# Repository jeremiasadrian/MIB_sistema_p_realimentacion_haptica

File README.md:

# MIB_sistema_p_realimentacion_haptica
**DESCRIPCION DEL REPOSITORIO.**
<p align="justify">
El presente respositorio corresponde al Proyecto asociado a la Tesis de la Maestría en Ingeniería Biomédica de la FI-UNER, titulada "Diseño de sistema háptico para realimentación táctil no invasiva en protesis de miembro superior". El mismo esta estructurado con cinco carpetas principales accecibles desde la raiz, con el siguiente contenido:
  
  + **Codigo-fuente:** Aquí podrá acceder a los códigos fuentes de prueba de la fuente de alimentación (en Arduino) y al código principal de PSoC4 sobre el cual funciones el Electroestimulador por corriente.
  + **Documentación:** Dentro podrá encontrar tres subcarpetas con información del **Anteproyecto** de la Tesis en cuestión; en **Datasheets_relevantes** estan las Hojas de Datos de los componentes principales del proyecto (PSoC4, transostires de alta tensión, regulador PWM de la fuente, sensor FSR); y finalmente en **Referencias** se encuentras las publicaciones que se mencionan en el Anteproyecto y propocionan la base de investigación sobre la que se simentó el presente desarrollo.
  + **Esquemativos-y-PCB:** En esta parte podrá acceder a los archivos generador por el sotfware **KiCAD 6.0** con los circuitos esquemáticos y PCB de las dos placas principales del proyecto, por un lado la **Fuente de Alimentación** y por otro la **Fuente de corriente con la interfaz de usuario**, ambos en su conjunto conforman el sistema de electroestimulación para la generación de la realimentación buscada.
  + **Resultados:** Aquí se ecuentras las imagenes y planillas de datos de los relevamientos llevado adelante a los largo del desarrollo, algunos sobre componentes específicos, asi como sobre el sistema o partes del sistema.
  + **Simulaciones:** En esta carpeta se podrán acceder a los archivos de simulación de distintas partes del circuito, mayormente implementadas en **Proteus VSM 8.13 SP1** aunque hay archivos en **LTSpice XVII**.

Cada carpeta pricipal tiene su **README.md** asociado con mas detalles sobre su contenido.
</p>

<h4 align="left">DESCRIPCION DEL PROYECTO.</h4>
<p align="justify"> 
Con el desarrollo de este proyecto se busca diseñar un sistema que permita generar una realimentación táctil efectiva, de manera no invasiva, aplicable a prótesis de miembro superior para la incorporación de sensibilidad táctil a la misma.
Considerando la totalidad del sistema, el mismo puede ser representado mediante los bloques funcionales presentados en la Figura 1:
</p>

<h4 align="center">Figura 1: Diagrama en bloques del sistema completo.</h4>

<p align="justify">
El primer bloque implementado (Sistema de Control), consta esencialmente de una placa de prototipado basada en un microcontrolador PSoC-4 de la empresa Cypress, bajo el código CY8CKIT-049-42xx, cuyo núcleo se vale del integrado CY8C4245AXI-483, el cual posee una estructura interna según el siguiente diagrama:
</p>

<h4 align="center">Figura 2: Diagrama en bloques del integrado CY8C4245AXI-483, núcleo de la placa de prototipado CY8CKIT-049-42xx de Cypress.</h4>

<p align="justify">
Junto con la placa mencionada, se encuentran conectados unos periféricos básicos para la interface del usuario con el menú de configuración. Puntualmente una pantallas LCD de 16x2 y tres pulsadores.
Mediante los comando ingresados con los mencionados pulsadores (tres) y la pantalla LCD, se interactúa con un menú que permite configurar los parámetros de electroestimulación, dentro de rangos de frecuencia y ciclos de trabajo discretos estandarizados y niveles de corriente limitados por hardware en el bloque de interface analógica. La forma de onda de la señal de electroestimulación es cuadrada-bipolar de valor medio nulo, con frecuencias de trabajo configurables entre los 278Hz y 1111Hz, y ciclos de trabajo de 8%, 12% y 16%, según se detallan en la Figura 3 y Tabla 1 siguientes:
</p>
<p align="center">

    </div
</p>
<h4 align="left">Figura 3: Forma de onda de electroestimulación por corriente. Tabla 1: Periodo, frec. y ciclo de trabajo para electroestimulación.</h4>
<p align="justify">
Tanto la estructura de la señal como los parámetros característicos de la misma, tienen su fundamento en antecedentes de trabajos basados en el uso de electroestimulación por corriente para la generación de sensación táctil en no videntes o disminuidos visuales, a fin de implementar dispositivos para la lectura de texto Braille digitalizado, como se expone en [1] y [2].
El segundo bloque implementado (Interface Analógica) puede dividirse en dos etapas, en primera instancia y conectada directamente con el Sistema de Control, se encuentra un circuito basado en AO, que adaptan la señal del IDAC (Conversor Digital Analógico de Corriente) del PSoC 4, para la interacción con la fuente de corriente de salida, que conecta directamente con el usuario (sujeto que recibe la electroestimulación) y generan la limitación de corriente de salida por hardware.
En segundo lugar se encuentra la fuente de corriente propiamente dicha, compuesta por seis transistores BJT complementarios, de alta tensión de colector-emisor y baja potencia. Esta última etapa se nutre de una fuente partida de alta tensión (±150V) para aplicar la corriente de electroestimulación de manera efectiva, para resistencias de interface electrodo-piel de hasta 75kΩ.
En función de lo detallado precedentemente, se desprende que el PCB necesario corresponde a una etapa del desarrollo de la Tesis, a los fines de dinamizar las pruebas del prototipo previo a su ensayo en pacientes. El mismo debe contener los dos bloques descriptos anteriormente, debiendo manipular señales rectangulares de hasta 1,1kHz y con los recaudos necesarios para los tramos de alta tensión de alimentación, tanto en la selección de los transistores de salida como en el distanciamiento entre pistas en la región del circuito correspondiente.
</p>

<h4 align="left">REFERENCIAS.</h4>

[1-Electrocutaneous_Stimulation_System_for_Braille_Reading-2010](Documentacion/Referencias/[11]Electrocutaneous_Stimulation_System_for_Braille_Reading-2010.pdf)

[2-Electrical_stimulation_of_mechanoreceptors-2011](Documentacion/Referencias/[10]Electrical_stimulation_of_mechanoreceptors-2011.pdf)

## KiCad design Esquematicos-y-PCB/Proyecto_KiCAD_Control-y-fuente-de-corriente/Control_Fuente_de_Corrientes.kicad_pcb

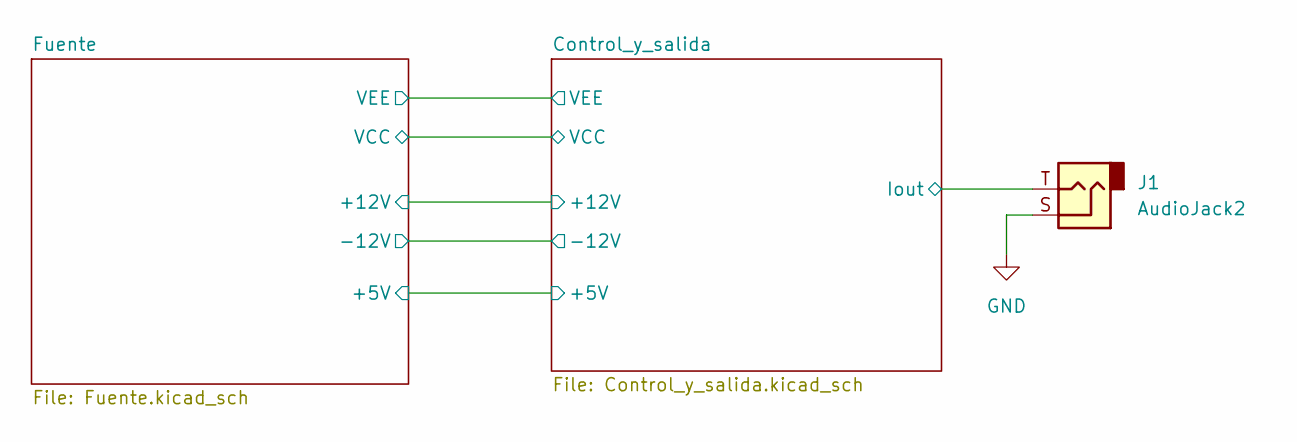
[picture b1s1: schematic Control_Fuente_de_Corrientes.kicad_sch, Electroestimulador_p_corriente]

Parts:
J1: AudioJack2; Jack_3.5mm_Ledino_KB3SPRS_Horizontal

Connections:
/Control_y_salida/Iout: J1.T; also elsewhere on the board
GND: J1.S; also elsewhere on the board

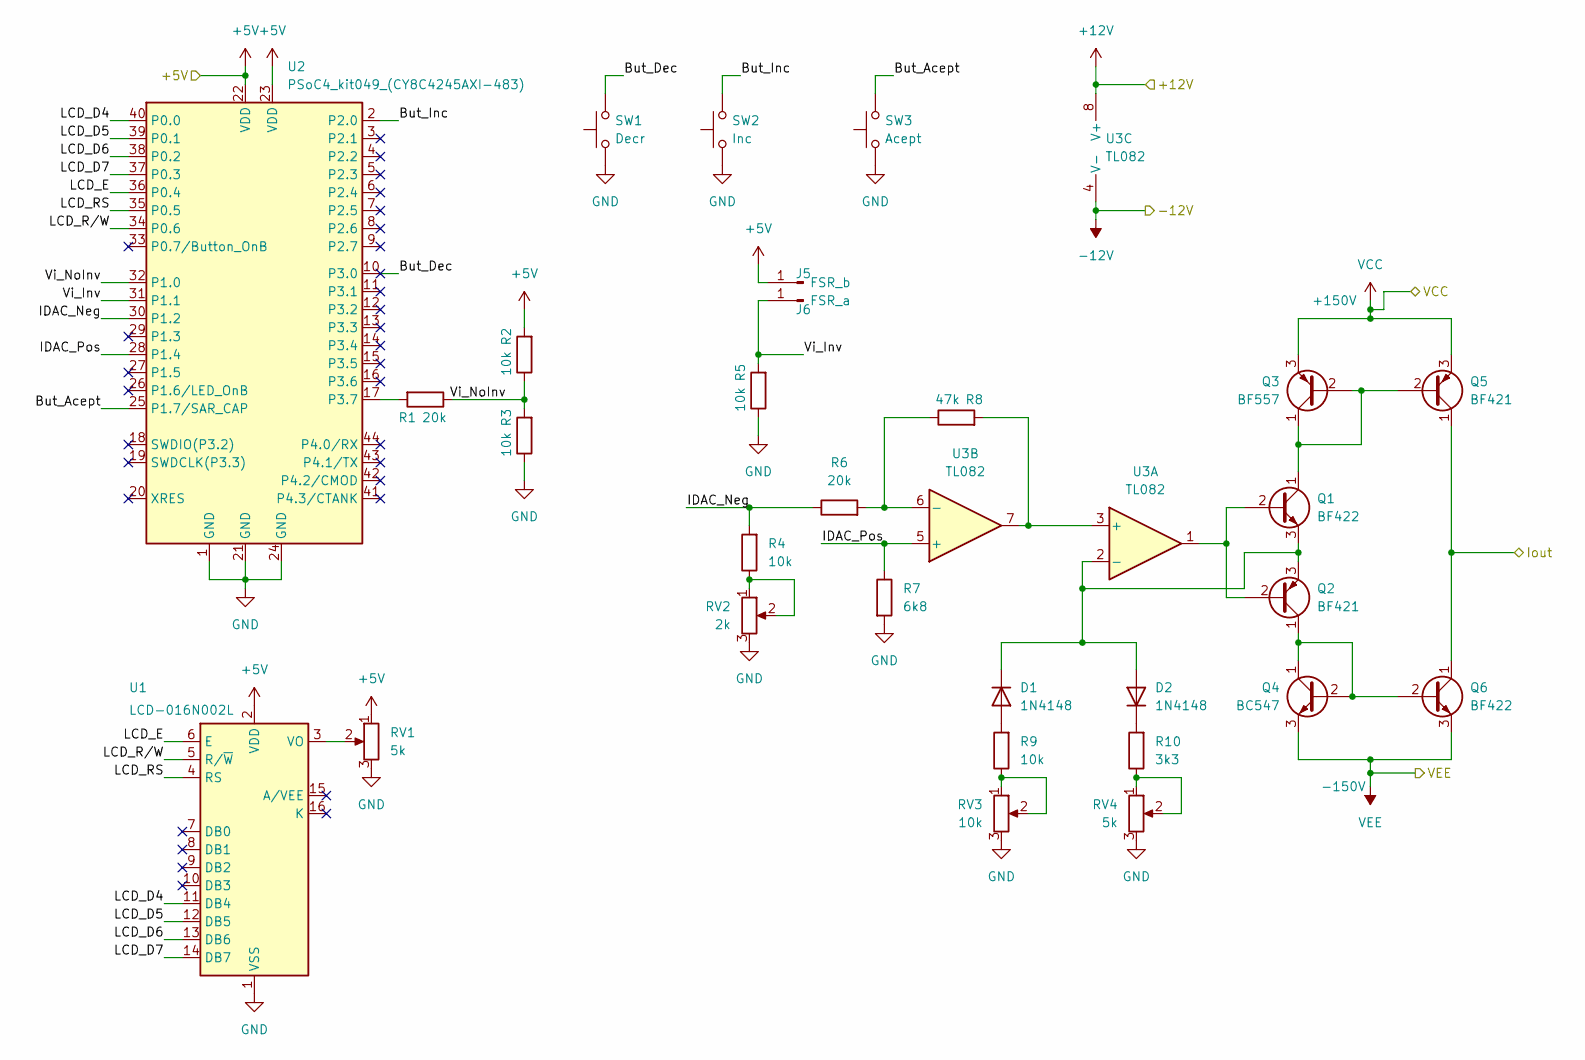
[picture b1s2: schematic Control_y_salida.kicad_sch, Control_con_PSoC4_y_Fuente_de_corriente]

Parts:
D1, D2: 1N4148; D_DO-41_SOD81_P7.62mm_Horizontal
J5: FSR_b; Pin_D0.9mm_L10.0mm_W2.4mm_FlatFork
J6: FSR_a; Pin_D0.9mm_L10.0mm_W2.4mm_FlatFork
Q1, Q6: BF422; BF42X
Q2, Q5: BF421; BF42X
Q3: BF557; BF42X
Q4: BC547; BF42X
R1, R6: 20k; R_Axial_DIN0207_L6.3mm_D2.5mm_P10.16mm_Horizontal; Tolerancia 1%
R2, R3, R4, R5, R9: 10k; R_Axial_DIN0207_L6.3mm_D2.5mm_P10.16mm_Horizontal; Tolerancia 1%
R7: 6k8; R_Axial_DIN0207_L6.3mm_D2.5mm_P10.16mm_Horizontal; Tolerancia 1%
R8: 47k; R_Axial_DIN0207_L6.3mm_D2.5mm_P10.16mm_Horizontal; Tolerancia 1%
R10: 3k3; R_Axial_DIN0207_L6.3mm_D2.5mm_P10.16mm_Horizontal; Tolerancia 1%
RV1, RV4: 5k; Potentiometer_Bourns_3296W_Vertical
RV2: 2k; Potentiometer_Bourns_3296W_Vertical
RV3: 10k; Potentiometer_Bourns_3296W_Vertical
SW1: Decr; SW_PUSH_6mm_H7.3mm
SW2: Inc; SW_PUSH_6mm_H7.3mm
SW3: Acept; SW_PUSH_6mm_H7.3mm
U1: LCD-016N002L; LCD_pinsonly
U2: PSoC4_kit049_(CY8C4245AXI-483); PinSocket_2x22_P2.54mm_Vertical_3
U3: TL082; DIP-8_W10.16mm_LongPads

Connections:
+5V: J5.1, R2.2, RV1.1, U1.2 (VDD), U2.22 (VDD), U2.23 (VDD); also elsewhere on the board
+12V: U3.8 (V+); also elsewhere on the board
-12V: U3.4 (V-); also elsewhere on the board
/Control_y_salida/But_Acept: SW3.2, U2.25 (P1.7/SAR_CAP)
/Control_y_salida/But_Dec: SW1.2, U2.10 (P3.0)
/Control_y_salida/But_Inc: SW2.2, U2.2 (P2.0)
/Control_y_salida/IDAC_Neg: R4.2, R6.1, U2.30 (P1.2)
/Control_y_salida/IDAC_Pos: R7.1, U2.28 (P1.4), U3.5 (+)
/Control_y_salida/Iout: Q5.1 (C), Q6.1 (C); also elsewhere on the board
/Control_y_salida/LCD_D4: U1.11 (DB4), U2.40 (P0.0)
/Control_y_salida/LCD_D5: U1.12 (DB5), U2.39 (P0.1)
/Control_y_salida/LCD_D6: U1.13 (DB6), U2.38 (P0.2)
/Control_y_salida/LCD_D7: U1.14 (DB7), U2.37 (P0.3)
/Control_y_salida/LCD_E: U1.6 (E), U2.36 (P0.4)
/Control_y_salida/LCD_RS: U1.4 (RS), U2.35 (P0.5)
/Control_y_salida/LCD_R/W: U1.5 (R/~W), U2.34 (P0.6)
/Control_y_salida/Vi_Inv: J6.1, R5.2, U2.31 (P1.1)
/Control_y_salida/Vi_NoInv: R1.1, R2.1, R3.2, U2.32 (P1.0)
GND: R3.1, R5.1, R7.2, RV1.3, RV2.3, RV3.3, RV4.3, SW1.1, SW2.1, SW3.1, U1.1 (VSS), U2.1 (GND), U2.21 (GND), U2.24 (GND); also elsewhere on the board
unnamed: D1.1 (K), D2.2 (A), Q1.3 (E), Q2.3 (E), U3.2 (-)
unnamed: D1.2 (A), R9.2
unnamed: D2.1 (K), R10.2
unnamed: Q1.1 (C), Q3.1 (C), Q3.2 (B), Q5.2 (B)
unnamed: Q1.2 (B), Q2.2 (B), U3.1
unnamed: Q2.1 (C), Q4.1 (C), Q4.2 (B), Q6.2 (B)
unnamed: R1.2, U2.17 (P3.7)
unnamed: R4.1, RV2.1, RV2.2
unnamed: R6.2, R8.1, U3.6 (-)
unnamed: R8.2, U3.3 (+), U3.7
unnamed: R9.1, RV3.1, RV3.2
unnamed: R10.1, RV4.1, RV4.2
unnamed: RV1.2, U1.3 (VO)
VCC: Q3.3 (E), Q5.3 (E); also elsewhere on the board
VEE: Q4.3 (E), Q6.3 (E); also elsewhere on the board

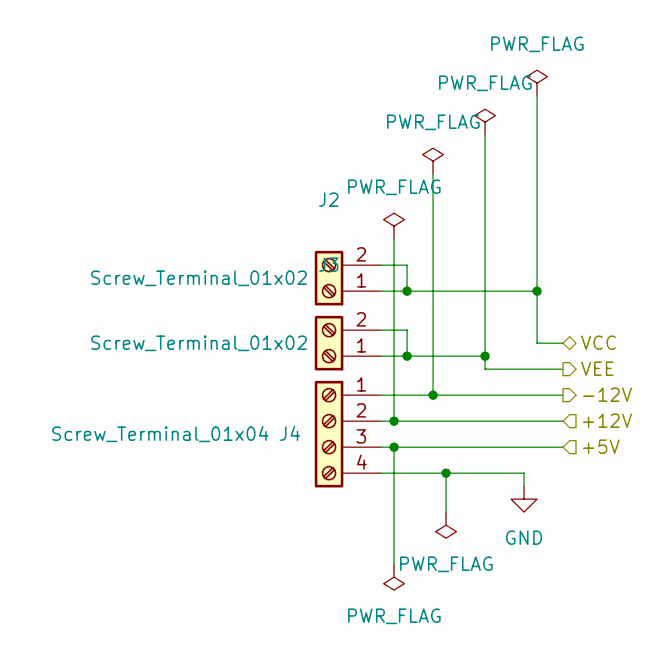
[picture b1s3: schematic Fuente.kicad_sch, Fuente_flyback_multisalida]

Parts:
J2, J3: Screw_Terminal_01x02; TerminalBlock_bornier-2_P5.08mm
J4: Screw_Terminal_01x04; TerminalBlock_bornier-4_P5.08mm

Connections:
+5V: J4.3; also elsewhere on the board
+12V: J4.2; also elsewhere on the board
-12V: J4.1; also elsewhere on the board
GND: J4.4; also elsewhere on the board
VCC: J2.1, J2.2; also elsewhere on the board
VEE: J3.1, J3.2; also elsewhere on the board

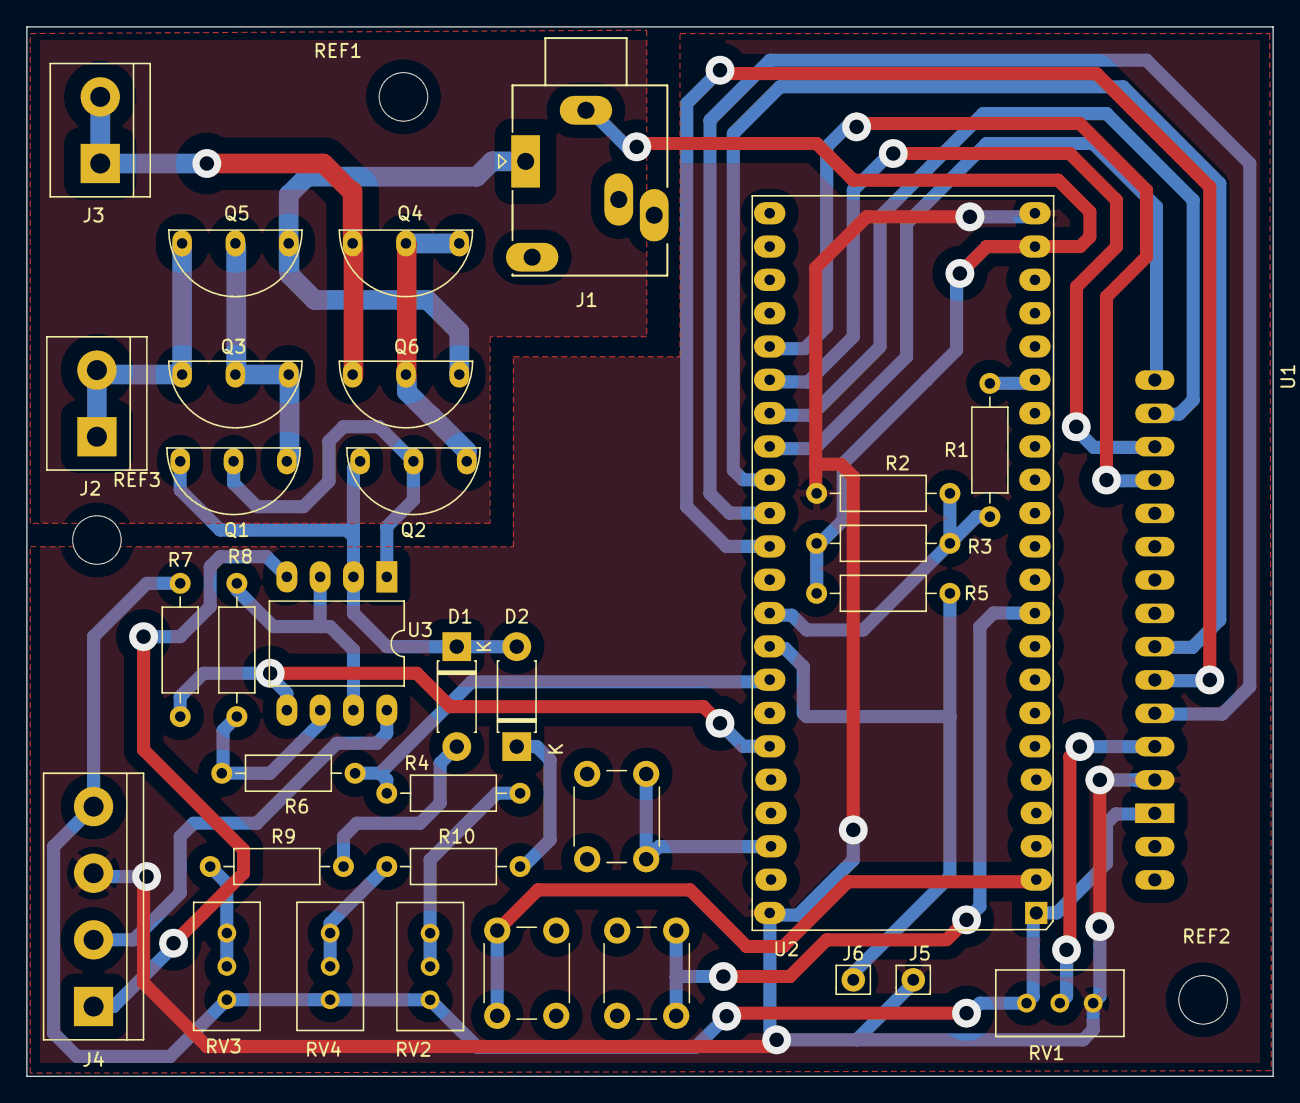
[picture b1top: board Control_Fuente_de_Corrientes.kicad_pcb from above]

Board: 2 copper layers, 95.0 x 80.0 mm, 37 parts (0 on the bottom side), 34 nets.

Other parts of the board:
REF1, REF2, REF3: MountingHole_3.7mm

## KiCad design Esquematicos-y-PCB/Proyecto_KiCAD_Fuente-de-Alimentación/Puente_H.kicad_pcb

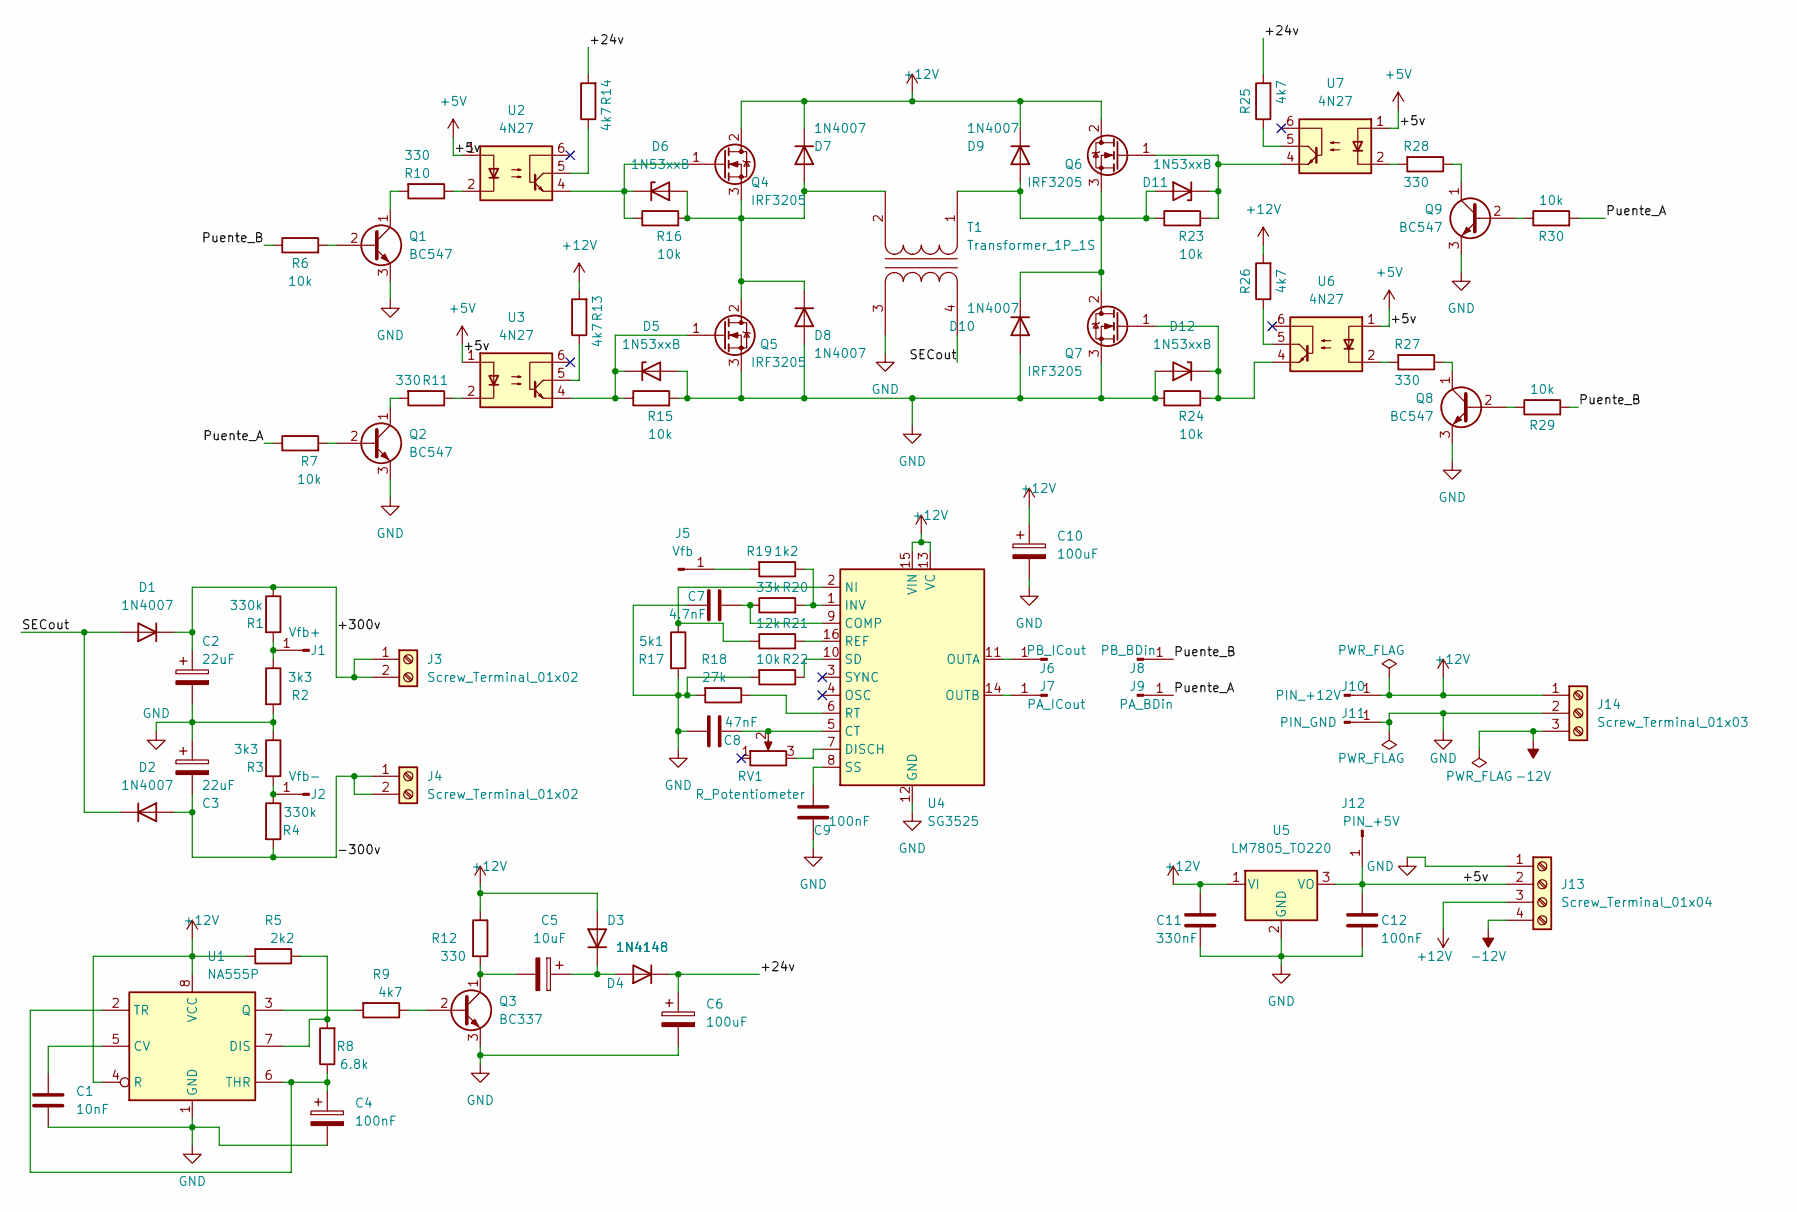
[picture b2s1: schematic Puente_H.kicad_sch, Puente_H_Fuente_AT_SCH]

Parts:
C1: 10nF; C_Disc_D5.0mm_W2.5mm_P2.50mm
C2, C3: 22uF; CP_Radial_D16.0mm_P7.50mm
C4, C9, C12: 100nF; C_Disc_D5.0mm_W2.5mm_P2.50mm
C5: 10uF; CP_Radial_D6.3mm_P2.50mm
C6, C10: 100uF; CP_Radial_D6.3mm_P2.50mm
C7: 4.7nF; C_Disc_D5.0mm_W2.5mm_P2.50mm
C8: 47nF; C_Disc_D5.0mm_W2.5mm_P2.50mm
C11: 330nF; C_Disc_D5.0mm_W2.5mm_P2.50mm
D1, D2, D7, D8, D9, D10: 1N4007; D_DO-41_SOD81_P10.16mm_Horizontal
D3, D4: 1N4148; D_DO-35_SOD27_P7.62mm_Horizontal
D5, D6, D11, D12: 1N53xxB; D_DO-35_SOD27_P7.62mm_Horizontal
J1: Vfb+; Pin_D0.7mm_L6.5mm_W1.8mm_FlatFork
J2: Vfb-; Pin_D0.7mm_L6.5mm_W1.8mm_FlatFork
J3, J4: Screw_Terminal_01x02; TerminalBlock_bornier-2_P5.08mm
J5: Vfb; Pin_D0.7mm_L6.5mm_W1.8mm_FlatFork
J6: PB_ICout; Pin_D0.7mm_L6.5mm_W1.8mm_FlatFork
J7: PA_ICout; Pin_D0.7mm_L6.5mm_W1.8mm_FlatFork
J8: PB_BDin; Pin_D0.7mm_L6.5mm_W1.8mm_FlatFork
J9: PA_BDin; Pin_D0.7mm_L6.5mm_W1.8mm_FlatFork
J10: PIN_+12V; Pin_D0.7mm_L6.5mm_W1.8mm_FlatFork
J11: PIN_GND; Pin_D0.7mm_L6.5mm_W1.8mm_FlatFork
J12: PIN_+5V; Pin_D0.7mm_L6.5mm_W1.8mm_FlatFork
J13: Screw_Terminal_01x04; TerminalBlock_bornier-4_P5.08mm
J14: Screw_Terminal_01x03; TerminalBlock_bornier-3_P5.08mm
Q1, Q2, Q8, Q9: BC547; TO-92_Inline_Wide
Q3: BC337; TO-92_Inline_Wide
Q4, Q5, Q6, Q7: IRF3205; TO-220-3_Vertical
R1, R4: 330k; R_Axial_DIN0207_L6.3mm_D2.5mm_P7.62mm_Horizontal
R2, R3: 3k3; R_Axial_DIN0207_L6.3mm_D2.5mm_P7.62mm_Horizontal
R5: 2k2; R_Axial_DIN0207_L6.3mm_D2.5mm_P7.62mm_Horizontal
R6, R7, R15, R16, R22, R23, R24, R29, R30: 10k; R_Axial_DIN0207_L6.3mm_D2.5mm_P7.62mm_Horizontal
R8: 6.8k; R_Axial_DIN0207_L6.3mm_D2.5mm_P7.62mm_Horizontal
R9, R13, R14, R25, R26: 4k7; R_Axial_DIN0207_L6.3mm_D2.5mm_P7.62mm_Horizontal
R10, R11, R12, R27, R28: 330; R_Axial_DIN0207_L6.3mm_D2.5mm_P7.62mm_Horizontal
R17: 5k1; R_Axial_DIN0207_L6.3mm_D2.5mm_P7.62mm_Horizontal
R18: 27k; R_Axial_DIN0207_L6.3mm_D2.5mm_P7.62mm_Horizontal
R19: 1k2; R_Axial_DIN0207_L6.3mm_D2.5mm_P7.62mm_Horizontal
R20: 33k; R_Axial_DIN0207_L6.3mm_D2.5mm_P7.62mm_Horizontal
R21: 12k; R_Axial_DIN0207_L6.3mm_D2.5mm_P7.62mm_Horizontal
RV1: R_Potentiometer; Potentiometer_Bourns_3296W_Vertical
T1: Transformer_1P_1S; Transformer_1S_2P
U1: NA555P; DIP-8_W7.62mm
U2, U3, U6, U7: 4N27; DIP-6_W7.62mm
U4: SG3525; DIP-16_W7.62mm_LongPads
U5: LM7805_TO220; TO-220-3_Vertical

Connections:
+5V: C12.1, J12.1, J13.2, U2.1, U3.1, U5.3 (VO), U6.1, U7.1
+12V: C10.1, C11.1, D3.2 (A), D7.1 (K), D9.1 (K), J10.1, J13.3, J14.1, Q4.2 (D), Q6.2 (D), R5.2, R12.1, R13.2, R26.2, U1.4 (R), U1.8 (VCC), U4.13 (VC), U4.15 (VIN), U5.1 (VI)
-12V: J13.4, J14.3
/+24v: C6.1, D4.1 (K), R14.2, R25.2
/+300v: C2.1, D1.1 (K), J3.1, J3.2, R1.1
/-300v: C3.2, D2.2 (A), J4.1, J4.2, R4.2
/Puente_A: J9.1, R7.1, R30.2
/Puente_B: J8.1, R6.1, R29.2
/SECout: D1.2 (A), D2.1 (K), T1.4 (SB)
GND: C1.2, C2.2, C3.1, C4.2, C6.2, C7.2, C8.1, C9.1, C10.2, C11.2, C12.2, D5.2 (A), D8.2 (A), D10.2 (A), D12.2 (A), J11.1, J13.1, J14.2, Q1.3 (E), Q2.3 (E), Q3.3 (E), Q5.3 (S), Q7.3 (S), Q8.3 (E), Q9.3 (E), R2.2, R3.1, R15.2, R17.2, R18.2, R22.2, R24.1, T1.3 (SA), U1.1 (GND), U4.12 (GND), U5.2 (GND)
unnamed: C1.1, U1.5 (CV)
unnamed: C4.1, R8.1, U1.2 (TR), U1.6 (THR)
unnamed: C5.1, D3.1 (K), D4.2 (A)
unnamed: C5.2, Q3.1 (C), R12.2
unnamed: C7.1, R20.1, U4.9 (COMP)
unnamed: C8.2, RV1.2, U4.5 (CT)
unnamed: C9.2, U4.8 (SS)
unnamed: D5.1 (K), Q5.1 (G), R15.1, U3.4
unnamed: D6.1 (K), Q4.1 (G), R16.1, U2.4
unnamed: D6.2 (A), D7.2 (A), D8.1 (K), Q4.3 (S), Q5.2 (D), R16.2, T1.2 (AB)
unnamed: D9.2 (A), D10.1 (K), D11.2 (A), Q6.3 (S), Q7.2 (D), R23.1, T1.1 (AA)
unnamed: D11.1 (K), Q6.1 (G), R23.2, U7.4
unnamed: D12.1 (K), Q7.1 (G), R24.2, U6.4
unnamed: J1.1, R1.2, R2.1
unnamed: J2.1, R3.2, R4.1
unnamed: J5.1, R19.2
unnamed: J6.1, U4.11 (OUTA)
unnamed: J7.1, U4.14 (OUTB)
unnamed: Q1.1 (C), R10.2
unnamed: Q1.2 (B), R6.2
unnamed: Q2.1 (C), R11.2
unnamed: Q2.2 (B), R7.2
unnamed: Q3.2 (B), R9.1
unnamed: Q8.1 (C), R27.1
unnamed: Q8.2 (B), R29.1
unnamed: Q9.1 (C), R28.1
unnamed: Q9.2 (B), R30.1
unnamed: R5.1, R8.2, U1.7 (DIS)
unnamed: R9.2, U1.3 (Q)
unnamed: R10.1, U2.2
unnamed: R11.1, U3.2
unnamed: R13.1, U3.5
unnamed: R14.1, U2.5
unnamed: R17.1, R21.1, U4.2 (NI)
unnamed: R18.1, U4.6 (RT)
unnamed: R19.1, R20.2, U4.1 (INV)
unnamed: R21.2, U4.16 (REF)
unnamed: R22.1, U4.10 (SD)
unnamed: R25.1, U7.5
unnamed: R26.1, U6.5
unnamed: R27.2, U6.2
unnamed: R28.2, U7.2
unnamed: RV1.3, U4.7 (DISCH)

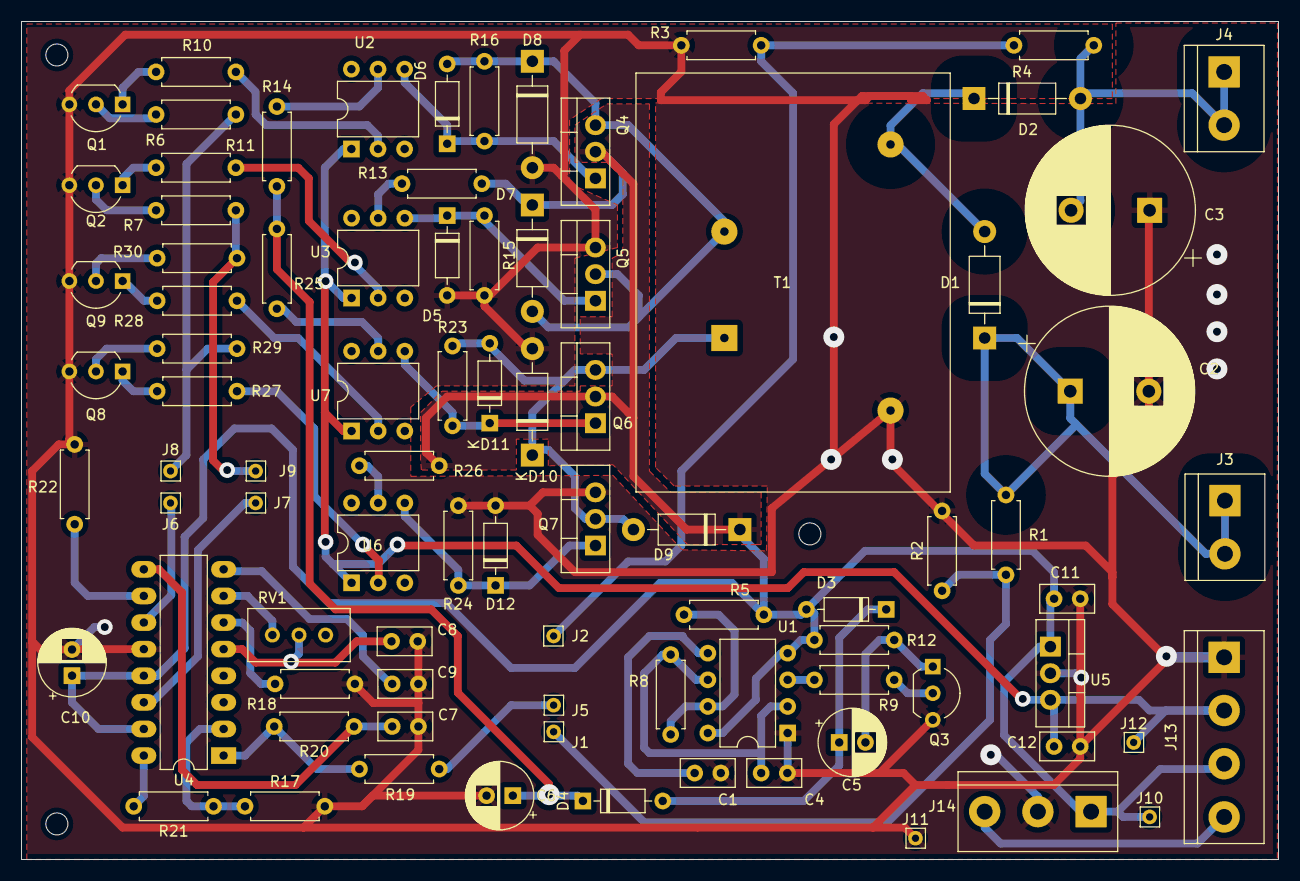
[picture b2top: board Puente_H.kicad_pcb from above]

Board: 2 copper layers, 120.0 x 80.0 mm, 89 parts (0 on the bottom side), 53 nets.

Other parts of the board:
REF01, REF02, REF03: MountingHole_2.1mm

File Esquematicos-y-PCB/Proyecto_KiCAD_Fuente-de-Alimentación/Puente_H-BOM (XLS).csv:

Source: C:\Users\Jeremias\Documents\GitHub\jeremiasadrian\Tesis MIB\Proyecto de Tesis\TESIS - Desarrollo\PCB\Puente H p Fuente AT\Puente_H\Puente_H.kicad_sch;;;
Date: 18/1/2024  09:40:58;;;
Programa: Eeschema (6.0.7);;;
Generator: D:\Programas\KiCad\6.0\bin\scripting\plugins/bom_csv_grouped_by_value_with_fp.py;;;
Cantidad de componentes: 86;;;
Ref. del componente;Cantidad;Valor;Footprint
C1;1;10nF;Capacitor_THT:C_Disc_D5.0mm_W2.5mm_P2.50mm
C2, C3;2;"22uF; 450v";Capacitor_THT:CP_Radial_D16.0mm_P7.50mm
C4, C9, C12;3;100nF;Capacitor_THT:C_Disc_D5.0mm_W2.5mm_P2.50mm
C5;1;"10uF; 16v";Capacitor_THT:CP_Radial_D6.3mm_P2.50mm
C6;1;"100uF; 35v/50v";Capacitor_THT:CP_Radial_D6.3mm_P2.50mm
C7;1;4.7nF;Capacitor_THT:C_Disc_D5.0mm_W2.5mm_P2.50mm
C8;1;39nF;Capacitor_THT:C_Disc_D5.0mm_W2.5mm_P2.50mm
C10;1;"100uF; 16v";Capacitor_THT:C_Disc_D5.0mm_W2.5mm_P2.50mm
C11;1;330nF;Capacitor_THT:C_Disc_D5.0mm_W2.5mm_P2.50mm
D1, D2, D7, D8, D9, D10;6;1N4007;Diode_THT:D_DO-41_SOD81_P10.16mm_Horizontal
D3, D4;2;1N4148;Diode_THT:D_DO-35_SOD27_P7.62mm_Horizontal
D5, D6, D11, D12;4;1N5240B;"Diode_THT:D_DO-35_SOD27_P7.62mm_Horizontal; zener x10v"
J1;1;Vfb+;Connector_Pin:Pin_D0.7mm_L6.5mm_W1.8mm_FlatFork
J2;1;Vfb-;Connector_Pin:Pin_D0.7mm_L6.5mm_W1.8mm_FlatFork
J3, J4;2;Screw_Terminal_01x02;TerminalBlock:TerminalBlock_bornier-2_P5.08mm
J5;1;Vfb;Connector_Pin:Pin_D0.7mm_L6.5mm_W1.8mm_FlatFork
J6;1;PB_ICout;Connector_Pin:Pin_D0.7mm_L6.5mm_W1.8mm_FlatFork
J7;1;PA_ICout;Connector_Pin:Pin_D0.7mm_L6.5mm_W1.8mm_FlatFork
J8;1;PB_BDin;Connector_Pin:Pin_D0.7mm_L6.5mm_W1.8mm_FlatFork
J9;1;PA_BDin;Connector_Pin:Pin_D0.7mm_L6.5mm_W1.8mm_FlatFork
J10;1;PIN_+12V;Connector_Pin:Pin_D0.7mm_L6.5mm_W1.8mm_FlatFork
J11;1;PIN_GND;Connector_Pin:Pin_D0.7mm_L6.5mm_W1.8mm_FlatFork
J12;1;PIN_+5V;Connector_Pin:Pin_D0.7mm_L6.5mm_W1.8mm_FlatFork
J13;1;Screw_Terminal_01x04;TerminalBlock:TerminalBlock_bornier-4_P5.08mm
J14;1;Screw_Terminal_01x03;TerminalBlock:TerminalBlock_bornier-3_P5.08mm
Q1, Q2, Q8, Q9;4;BC547;Package_TO_SOT_THT:TO-92_Inline_Wide
Q3;1;BC337;Package_TO_SOT_THT:TO-92_Inline_Wide
Q4, Q5, Q6, Q7;4;IRF3205;Package_TO_SOT_THT:TO-220-3_Vertical
R1, R4;2;"330k; 1/4w ó 1/8w";Resistor_THT:R_Axial_DIN0207_L6.3mm_D2.5mm_P7.62mm_Horizontal
R2, R3;2;"3k3; 1/4w ó 1/8w";Resistor_THT:R_Axial_DIN0207_L6.3mm_D2.5mm_P7.62mm_Horizontal
R5;1;"2k2; 1/4w ó 1/8w";Resistor_THT:R_Axial_DIN0207_L6.3mm_D2.5mm_P7.62mm_Horizontal
R6, R7, R15, R16, R22, R24, R25, R30, R31;9;"10k; 1/4w ó 1/8w";Resistor_THT:R_Axial_DIN0207_L6.3mm_D2.5mm_P7.62mm_Horizontal
R8;1;"6.8k; 1/4w ó 1/8w";Resistor_THT:R_Axial_DIN0207_L6.3mm_D2.5mm_P7.62mm_Horizontal
R9, R13, R14, R26, R27;5;"4k7; 1/4w ó 1/8w";Resistor_THT:R_Axial_DIN0207_L6.3mm_D2.5mm_P7.62mm_Horizontal
R10, R11, R12, R28, R29;5;"330; 1/4w ó 1/8w";Resistor_THT:R_Axial_DIN0207_L6.3mm_D2.5mm_P7.62mm_Horizontal
R17;1;"5k1; 1/4w ó 1/8w";Resistor_THT:R_Axial_DIN0207_L6.3mm_D2.5mm_P7.62mm_Horizontal
R18;1;"27k; 1/4w ó 1/8w";Resistor_THT:R_Axial_DIN0207_L6.3mm_D2.5mm_P7.62mm_Horizontal
R19;1;"1k2; 1/4w ó 1/8w";Resistor_THT:R_Axial_DIN0207_L6.3mm_D2.5mm_P7.62mm_Horizontal
R20;1;"33k; 1/4w ó 1/8w";Resistor_THT:R_Axial_DIN0207_L6.3mm_D2.5mm_P7.62mm_Horizontal
R21;1;"12k; 1/4w ó 1/8w";Resistor_THT:R_Axial_DIN0207_L6.3mm_D2.5mm_P7.62mm_Horizontal
R23;1;"3k; 1/4w ó 1/8w";Resistor_THT:R_Axial_DIN0207_L6.3mm_D2.5mm_P7.62mm_Horizontal
T1;1;Transformer_1P_1S;Transformer_THT:Transformer_1S_2P
U1;1;NA555P;Package_DIP:DIP-8_W7.62mm
U2, U3, U6, U7;4;4N27;Package_DIP:DIP-6_W7.62mm
U4;1;SG3525;Package_DIP:DIP-16_W10.16mm_LongPads
U5;1;LM7805_TO220;Package_TO_SOT_THT:TO-220-3_Vertical

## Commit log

2024-03-17 Se incorpora contenido inicial
2024-03-17 Se agregan datos de pruebas en "Resultados/Pruebas"
2024-03-17 Agrega contenido inicial
    Incorpora contenido a todas las carpetas.
2024-03-17 Actualiza Readme
2024-03-17 cambio de formato en referencias
2024-03-18 Rename README_main.md to README.md
2024-05-27 Actualizar README.md
